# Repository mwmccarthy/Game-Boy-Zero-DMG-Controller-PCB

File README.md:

This is an updated version of the one Brian put up at Sudomod.com where I added 2 extra GND Pads for the L & R buttons and also fixed some Silk Screen test sizes and placement.

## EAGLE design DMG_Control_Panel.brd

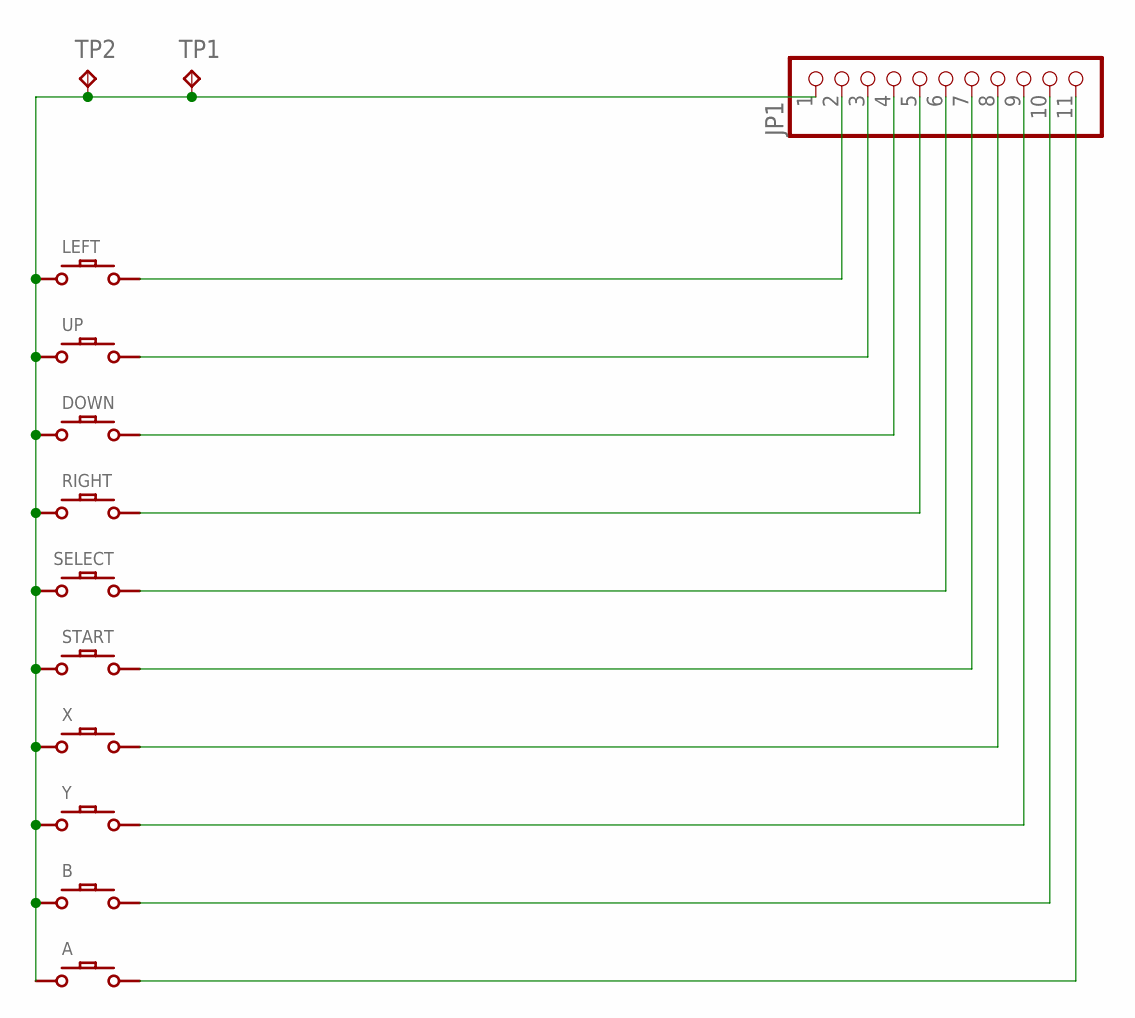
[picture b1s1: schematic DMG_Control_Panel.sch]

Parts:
A: DMG-BTN
B: DMG-BTN
DOWN: DMG-BTN
JP1: PINHD-1X11M; 1X11M
LEFT: DMG-BTN
RIGHT: DMG-BTN
SELECT: DMG-BTN; DMG-SEL
START: DMG-BTN; DMG-SEL
TP1, TP2: TPPAD1-13Y; P1-13Y
UP: DMG-BTN
X: DMG-BTN
Y: DMG-BTN

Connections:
GND: A.P$1, B.P$1, DOWN.P$1, JP1.1, LEFT.P$1, RIGHT.P$1, SELECT.P$2, START.P$2, TP1.TP, TP2.TP, UP.P$1, X.P$1, Y.P$1
unnamed: JP1.2, LEFT.P$2
unnamed: JP1.3, UP.P$2
unnamed: DOWN.P$2, JP1.4
unnamed: JP1.5, RIGHT.P$2
unnamed: JP1.6, SELECT.P$1
unnamed: JP1.7, START.P$1
unnamed: JP1.8, X.P$2
unnamed: JP1.9, Y.P$2
unnamed: B.P$2, JP1.10
unnamed: A.P$2, JP1.11

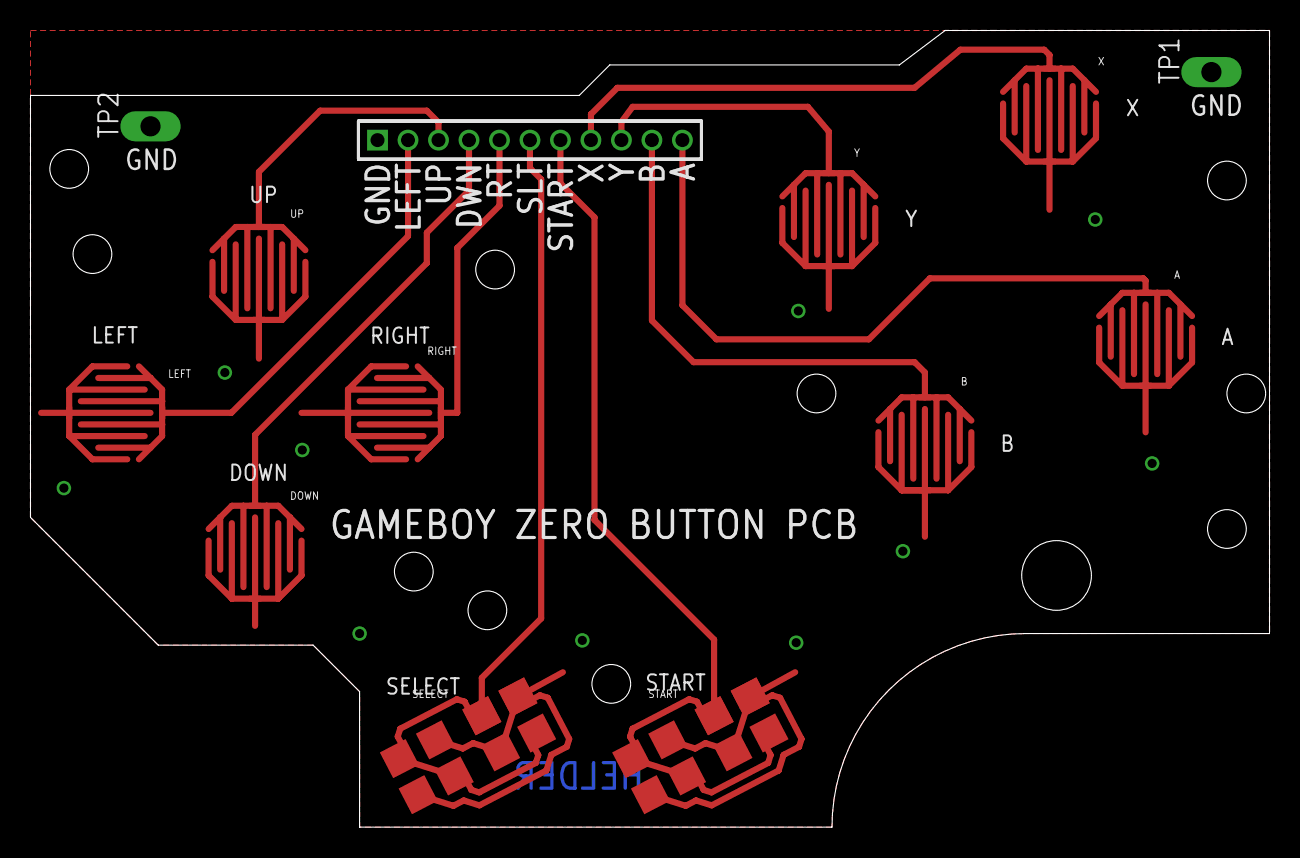
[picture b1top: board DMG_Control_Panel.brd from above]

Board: 2 copper layers, 81.3 x 52.3 mm, 13 parts (0 on the bottom side), 11 nets.

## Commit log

2016-05-06 Added files via upload
